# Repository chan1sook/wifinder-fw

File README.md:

# WiFinder Firmware

## espflash tools
https://www.espressif.com/en/support/download/other-tools

## Stucture
- squareline/ => UI Designed by [SquareLine Studio](https://squareline.io/)
- src/ => PlatformIO Arduino Codes
- hardware/ => Hardware Schematic

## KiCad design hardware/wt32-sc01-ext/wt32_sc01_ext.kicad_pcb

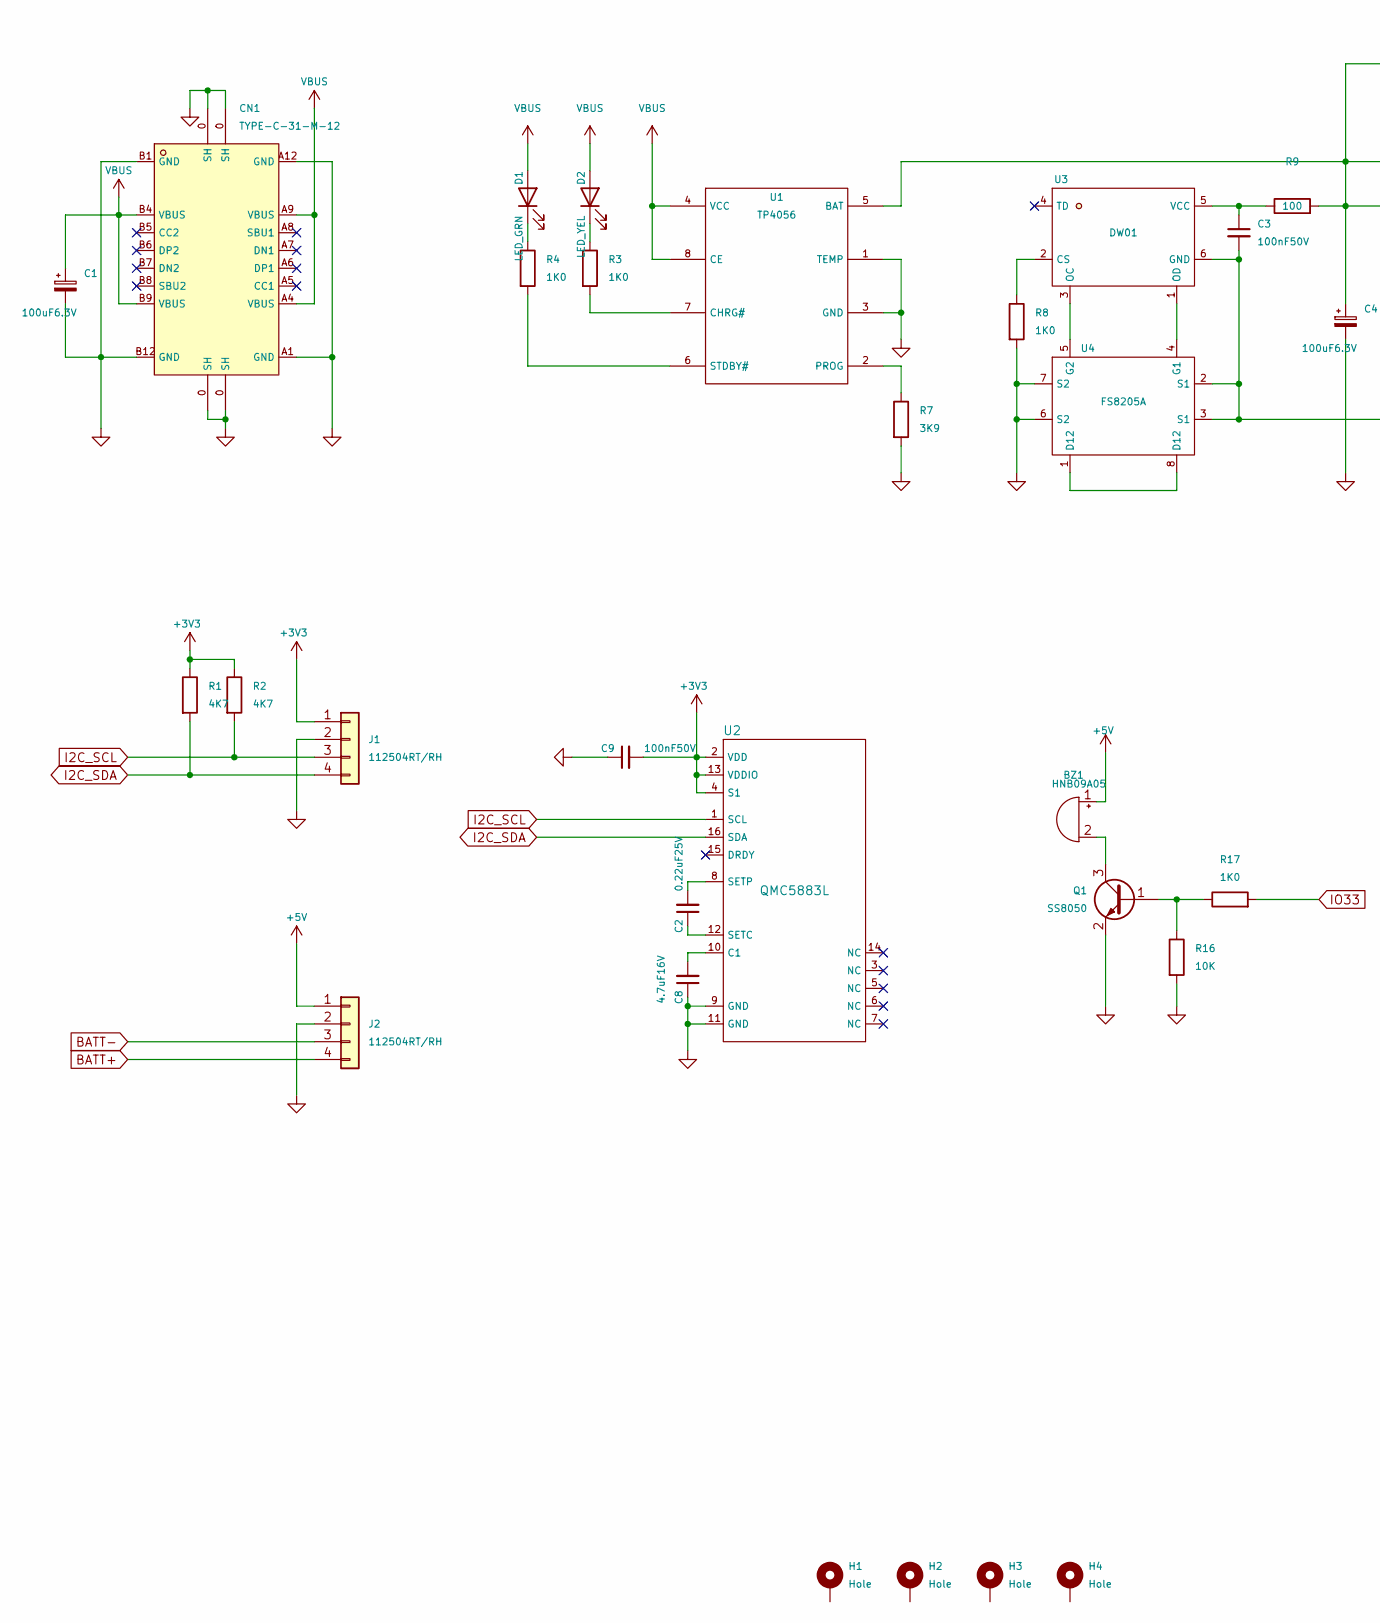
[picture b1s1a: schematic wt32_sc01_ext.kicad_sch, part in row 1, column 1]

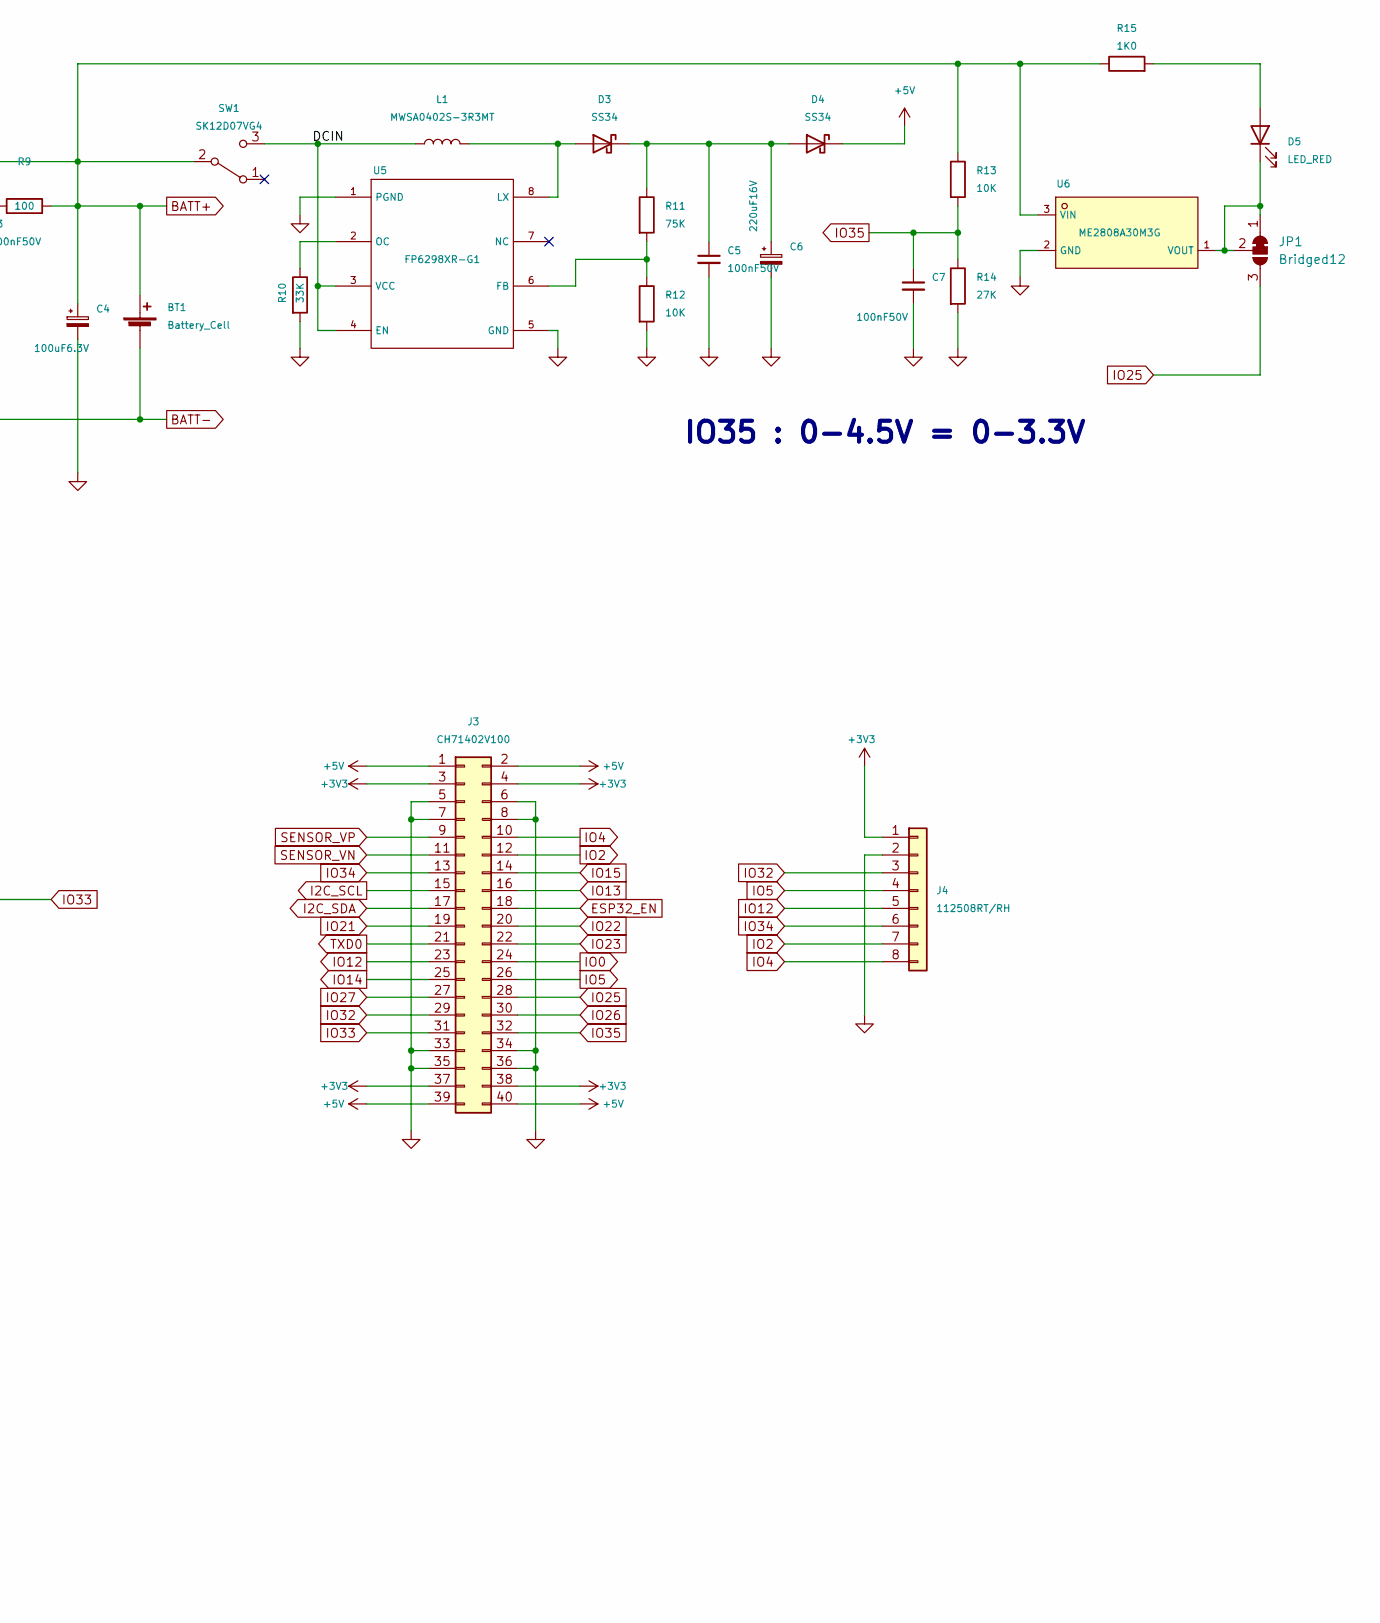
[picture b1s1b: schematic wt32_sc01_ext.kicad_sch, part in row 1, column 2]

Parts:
BT1: Battery_Cell; BatteryHolder_MPD_BH-18650-PC2
BZ1: HNB09A05; BUZ-TH_BD9.0-P5.00-D0.6-FD; LCSC C96493
C1, C4: 100uF6.3V; CAP-SMD_L3.5-W2.8; LCSC C16133
C2: 0.22uF25V; C_0603_1608Metric; LCSC C21120
C3, C5, C7, C9: 100nF50V; C_0603_1608Metric; LCSC C14663
C6: 220uF16V; CP_Elec_6.3x7.7; LCSC C96175
C8: 4.7uF16V; C_0603_1608Metric; LCSC C19666
CN1: TYPE-C-31-M-12; USB-C_SMD-TYPE-C-31-M-12; LCSC C165948
D1: LED_GRN; LED_0603_1608Metric; LCSC C72043
D2: LED_YEL; LED_0603_1608Metric; LCSC C72038
D3, D4: SS34; D_SMA; LCSC C8678
D5: LED_RED; LED_0603_1608Metric; LCSC C2286
H1, H2, H3, H4: Hole; MountingHole_3.2mm_M3
J1, J2: 112504RT/RH; JST_PH_S4B-PH-K_1x04_P2.00mm_Horizontal; LCSC C155878
J3: CH71402V100; PinHeader_2x20_P2.00mm_Vertical
J4: 112508RT/RH; JST_PH_S8B-PH-K_1x08_P2.00mm_Horizontal; LCSC C157915
JP1: Bridged12; SolderJumper-3_P1.3mm_Open_RoundedPad1.0x1.5mm_NumberLabels
L1: MWSA0402S-3R3MT; IND-SMD_L4.2-W4.4_MWSA0402S-XX; LCSC C408336
Q1: SS8050; SOT-23-3_L2.9-W1.3-P1.90-LS2.4-BR; LCSC C2150
R1, R2: 4K7; R_0603_1608Metric; LCSC C23162
R3, R4, R8, R15, R17: 1K0; R_0603_1608Metric; LCSC C21190
R7: 3K9; R_0603_1608Metric; LCSC C23018
R9: 100; R_0603_1608Metric; LCSC C22775
R10: 33K; R_0603_1608Metric; LCSC C4216
R11: 75K; R_0603_1608Metric; LCSC C23242
R12, R13, R16: 10K; R_0603_1608Metric; LCSC C25804
R14: 27K; R_0603_1608Metric; LCSC C22967
SW1: SK12D07VG4; SW-TH_SK12D07VG4; LCSC C393937
U1: TP4056; ESOP-8_L4.9-W3.9-P1.27-LS6.0-BL-EP; LCSC C16581
U2: QMC5883L; LGA-16_L3.0-W3.0-P0.50-BL_SQ; LCSC C976032
U3: DW01; SOT-23-6_L2.9-W1.6-P0.95-LS2.8-BR; LCSC C181096
U4: FS8205A; TSSOP-8_L4.4-W3.0-P0.65-LS6.4-BL-2; LCSC C16052
U5: FP6298XR-G1; SOP-8_L4.9-W3.9-P1.27-LS6.0-BL-EP; LCSC C88319
U6: ME2808A30M3G; SOT-23_L2.9-W1.3-P1.90-LS2.4-BR; LCSC C236747

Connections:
+3V3: C9.2, J1.1, J3.3, J3.4, J3.37, J3.38, J4.1, R1.1, R2.1, U2.2 (VDD), U2.4 (S1), U2.13 (VDDIO)
+5V: BZ1.1 (-), D4.1 (K), J2.1, J3.1, J3.2, J3.39, J3.40
/DCIN: L1.1, SW1.3 (C), U5.3 (VCC), U5.4 (EN)
BATT+: BT1.1 (+), C4.1, J2.4, R9.2, R13.1, R15.1, SW1.2 (B), U1.5 (BAT), U6.3 (VIN)
BATT-: BT1.2 (-), C3.2, J2.3, U3.6 (GND), U4.2 (S1), U4.3 (S1)
ESP32_EN: J3.18
GND: C1.2, C4.2, C5.2, C6.2, C7.2, C8.1, C9.1, CN1.0 (SH), CN1.A1 (GND), CN1.A12 (GND), CN1.B1 (GND), CN1.B12 (GND), J1.2, J2.2, J3.5, J3.6, J3.7, J3.8, J3.33, J3.34, J3.35, J3.36, J4.2, Q1.2 (E), R7.2, R8.2, R10.2, R12.2, R14.2, R16.2, U1.1 (TEMP), U1.3 (GND), U1.9 (EP), U2.9 (GND), U2.11 (GND), U4.6 (S2), U4.7 (S2), U5.1 (PGND), U5.5 (GND), U5.9 (EP), U6.2 (GND)
I2C_SCL: J1.3, J3.15, R2.2, U2.1 (SCL)
I2C_SDA: J1.4, J3.17, R1.2, U2.16 (SDA)
IO0: J3.24
IO2: J3.12, J4.7
IO4: J3.10, J4.8
IO5: J3.26, J4.4
IO12: J3.23, J4.5
IO13: J3.16
IO14: J3.25
IO15: J3.14
IO21: J3.19
IO22: J3.20
IO23: J3.22
IO25: J3.28, JP1.3 (B)
IO26: J3.30
IO27: J3.27
IO32: J3.29, J4.3
IO33: J3.31, R17.2
IO34: J3.13, J4.6
IO35: C7.1, J3.32, R13.2, R14.1
unnamed: BZ1.2 (+), Q1.3 (C)
unnamed: C2.1, U2.12 (SETC)
unnamed: C2.2, U2.8 (SETP)
unnamed: C3.1, R9.1, U3.5 (VCC)
unnamed: C5.1, C6.1, D3.1 (K), D4.2 (A), R11.1
unnamed: C8.2, U2.10 (C1)
unnamed: D1.1 (K), R4.1
unnamed: D2.1 (K), R3.1
unnamed: D3.2 (A), L1.2, U5.8 (LX)
unnamed: D5.1 (K), JP1.1 (A), JP1.2 (C), U6.1 (VOUT)
unnamed: D5.2 (A), R15.2
unnamed: Q1.1 (B), R16.1, R17.1
unnamed: R3.2, U1.7 (CHRG#)
unnamed: R4.2, U1.6 (STDBY#)
unnamed: R7.1, U1.2 (PROG)
unnamed: R8.1, U3.2 (CS)
unnamed: R10.1, U5.2 (OC)
unnamed: R11.2, R12.1, U5.6 (FB)
unnamed: U3.1 (OD), U4.4 (G1)
unnamed: U3.3 (OC), U4.5 (G2)
unnamed: U4.1 (D12), U4.8 (D12)
SENSOR_VN: J3.11
SENSOR_VP: J3.9
TXD0: J3.21
VBUS: C1.1, CN1.A4 (VBUS), CN1.A9 (VBUS), CN1.B4 (VBUS), CN1.B9 (VBUS), D1.2 (A), D2.2 (A), U1.4 (VCC), U1.8 (CE)

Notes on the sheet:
IO35 : 0-4.5V = 0-3.3V

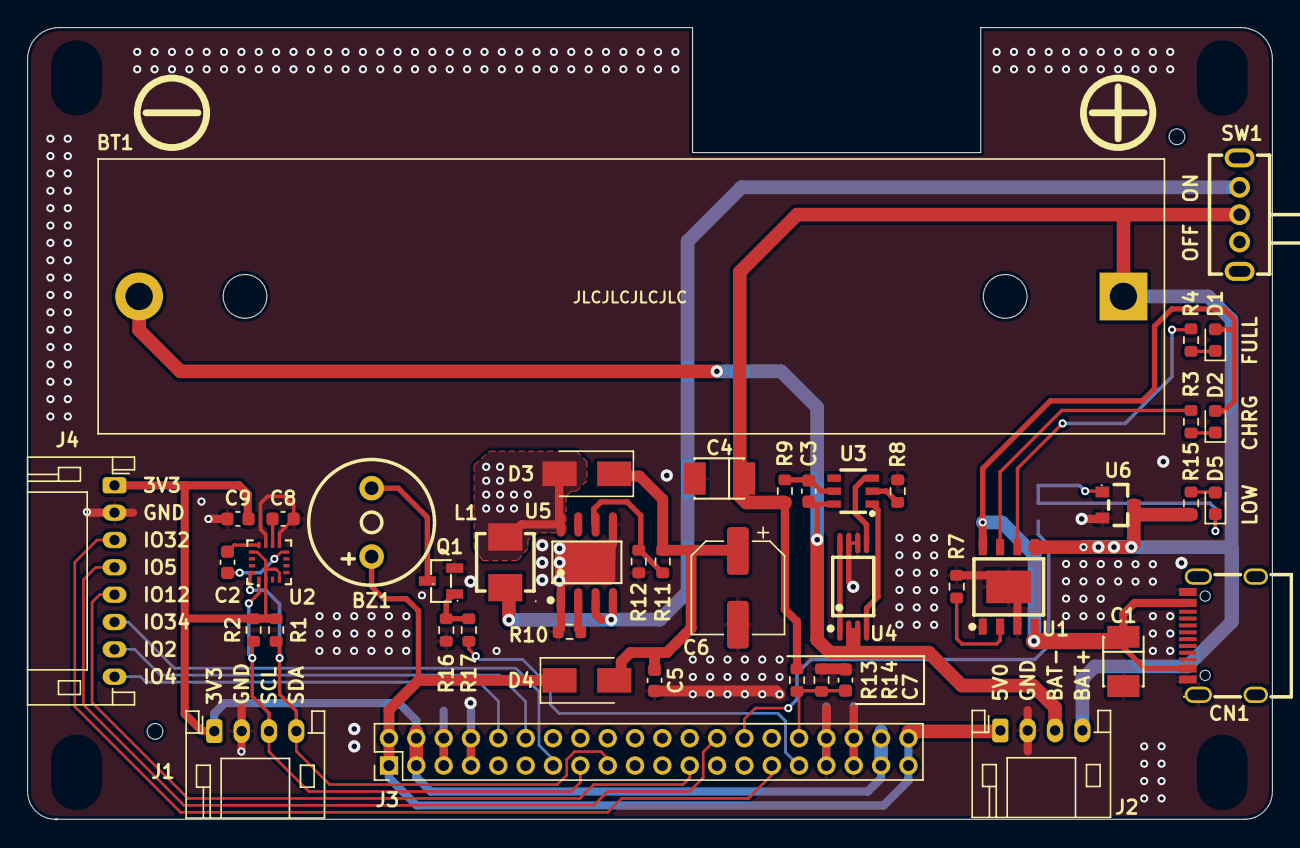
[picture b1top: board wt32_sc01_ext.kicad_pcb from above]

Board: 2 copper layers, 90.9 x 57.9 mm, 50 parts (1 on the bottom side), 39 nets.

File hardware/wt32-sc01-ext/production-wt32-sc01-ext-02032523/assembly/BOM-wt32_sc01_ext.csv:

Comment,Designator,Footprint,LCSC
100nF50V,"C3,C5,C7,C9",C_0603_1608Metric,C14663
112504RT/RH,"J1,J2",JST_PH_S4B-PH-K_1x04_P2.00mm_Horizontal,C155878
112508RT/RH,J4,JST_PH_S8B-PH-K_1x08_P2.00mm_Horizontal,C157915
FS8205A,U4,TSSOP-8_L4.4-W3.0-P0.65-LS6.4-BL-2,C16052
100uF6.3V,"C1,C4",CAP-SMD_L3.5-W2.8,C16133
TP4056,U1,ESOP-8_L4.9-W3.9-P1.27-LS6.0-BL-EP,C16581
TYPE-C-31-M-12,CN1,USB-C_SMD-TYPE-C-31-M-12,C165948
DW01,U3,SOT-23-6_L2.9-W1.6-P0.95-LS2.8-BR,C181096
4.7uF16V,C8,C_0603_1608Metric,C19666
0.22uF25V,C2,C_0603_1608Metric,C21120
1K0,"R15,R17,R3,R4,R8",R_0603_1608Metric,C21190
SS8050,Q1,SOT-23-3_L2.9-W1.3-P1.90-LS2.4-BR,C2150
100,R9,R_0603_1608Metric,C22775
LED_RED,D5,LED_0603_1608Metric,C2286
27K,R14,R_0603_1608Metric,C22967
3K9,R7,R_0603_1608Metric,C23018
4K7,"R1,R2",R_0603_1608Metric,C23162
75K,R11,R_0603_1608Metric,C23242
ME2808A30M3G,U6,SOT-23_L2.9-W1.3-P1.90-LS2.4-BR,C236747
10K,"R12,R13,R16",R_0603_1608Metric,C25804
SK12D07VG4,SW1,SW-TH_SK12D07VG4,C393937
MWSA0402S-3R3MT,L1,IND-SMD_L4.2-W4.4_MWSA0402S-XX,C408336
33K,R10,R_0603_1608Metric,C4216
LED_YEL,D2,LED_0603_1608Metric,C72038
LED_GRN,D1,LED_0603_1608Metric,C72043
SS34,"D3,D4",D_SMA,C8678
FP6298XR-G1,U5,SOP-8_L4.9-W3.9-P1.27-LS6.0-BL-EP,C88319
220uF16V,C6,CP_Elec_6.3x7.7,C96175
HNB09A05,BZ1,BUZ-TH_BD9.0-P5.00-D0.6-FD,C96493
QMC5883L,U2,LGA-16_L3.0-W3.0-P0.50-BL_SQ,C976032
Hole,H4,MountingHole_3.2mm_M3,
CH71402V100,J3,PinHeader_2x20_P2.00mm_Vertical,
Battery_Cell,BT1,BatteryHolder_MPD_BH-18650-PC2,
Hole,H3,MountingHole_3.2mm_M3,
Hole,H1,MountingHole_3.2mm_M3,
Hole,H2,MountingHole_3.2mm_M3,
Bridged12,JP1,SolderJumper-3_P1.3mm_Open_RoundedPad1.0x1.5mm_NumberLabels,

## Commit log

2022-10-02 1.0.1
2022-10-07 v1.1.0
2022-10-13 v1.1.1
2022-10-14 v1.2.0
2022-10-18 v1.3.0
2023-01-13 v1.4.0
2023-01-13 Remove Debug
2023-01-13 v1.4.1
2023-01-13 hotfix
2023-01-15 v.1.4.2
2023-01-24 v1.5.0
2023-02-01 v1.5.1
2023-03-01 v.1.5.2
2023-06-13 Add Hardware Schematic
